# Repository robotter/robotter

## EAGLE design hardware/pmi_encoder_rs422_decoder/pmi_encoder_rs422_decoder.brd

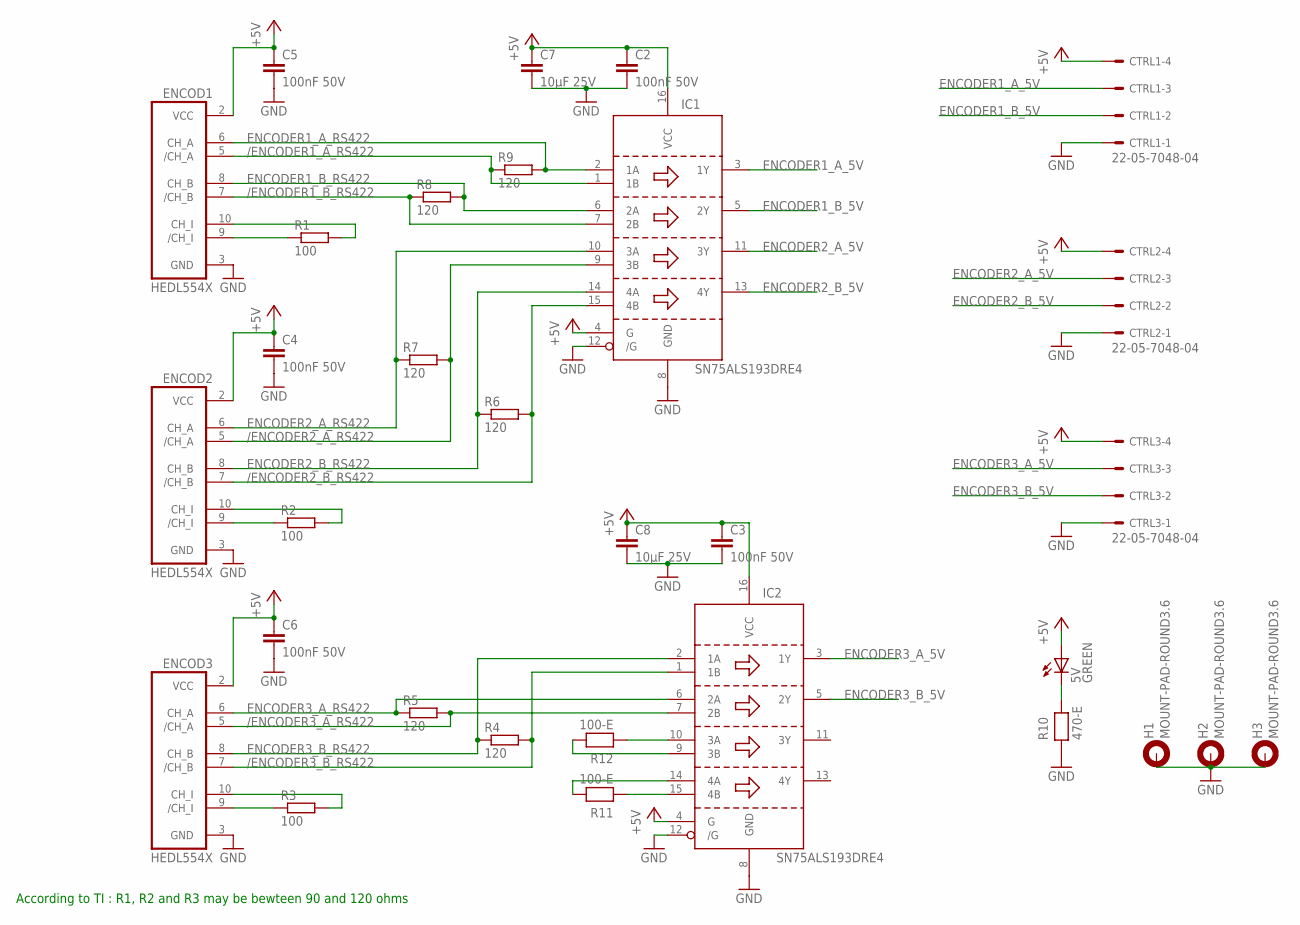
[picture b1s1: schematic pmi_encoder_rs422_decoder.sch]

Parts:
5V: GREEN; CHIP-LED0805
C2, C3, C4, C5, C6: 100nF 50V; C0805
C7, C8: 10µF 25V; C1210
CTRL1, CTRL2, CTRL3: 22-05-7048-04; 7395-04
ENCOD1, ENCOD2, ENCOD3: HEDL554X; ML10
H1, H2, H3: MOUNT-PAD-ROUND3.6; 3,6-PAD
IC1, IC2: SN75ALS193DRE4; SO16
R1, R2, R3: 100; 0207/7
R4, R5, R6, R7, R8, R9: 120; 0207/7
R10: 470-E; R0805
R11, R12: 100-E; R0805

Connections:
+5V: 5V.A, C2.1, C3.1, C4.1, C5.1, C6.1, C7.1, C8.1, CTRL1.4, CTRL2.4, CTRL3.4, ENCOD1.2 (VCC), ENCOD2.2 (VCC), ENCOD3.2 (VCC), IC1.4 (G), IC1.16 (VCC), IC2.4 (G), IC2.16 (VCC)
/ENCODER1_A_RS422: ENCOD1.5 (/CH_A), IC1.1 (1B), R9.1
/ENCODER1_B_RS422: ENCOD1.7 (/CH_B), IC1.7 (2B), R8.1
/ENCODER2_A_RS422: ENCOD2.5 (/CH_A), IC1.9 (3B), R7.2
/ENCODER2_B_RS422: ENCOD2.7 (/CH_B), IC1.15 (4B), R6.2
/ENCODER3_A_RS422: ENCOD3.5 (/CH_A), IC2.7 (2B), R5.2
/ENCODER3_B_RS422: ENCOD3.7 (/CH_B), IC2.1 (1B), R4.2
ENCODER1_A_5V: CTRL1.3, IC1.3 (1Y)
ENCODER1_A_RS422: ENCOD1.6 (CH_A), IC1.2 (1A), R9.2
ENCODER1_B_5V: CTRL1.2, IC1.5 (2Y)
ENCODER1_B_RS422: ENCOD1.8 (CH_B), IC1.6 (2A), R8.2
ENCODER2_A_5V: CTRL2.3, IC1.11 (3Y)
ENCODER2_A_RS422: ENCOD2.6 (CH_A), IC1.10 (3A), R7.1
ENCODER2_B_5V: CTRL2.2, IC1.13 (4Y)
ENCODER2_B_RS422: ENCOD2.8 (CH_B), IC1.14 (4A), R6.1
ENCODER3_A_5V: CTRL3.3, IC2.3 (1Y)
ENCODER3_A_RS422: ENCOD3.6 (CH_A), IC2.6 (2A), R5.1
ENCODER3_B_5V: CTRL3.2, IC2.5 (2Y)
ENCODER3_B_RS422: ENCOD3.8 (CH_B), IC2.2 (1A), R4.1
GND: C2.2, C3.2, C4.2, C5.2, C6.2, C7.2, C8.2, CTRL1.1, CTRL2.1, CTRL3.1, ENCOD1.3 (GND), ENCOD2.3 (GND), ENCOD3.3 (GND), H1.B3,6, H2.B3,6, H3.B3,6, IC1.8 (GND), IC1.12 (/G), IC2.8 (GND), IC2.12 (/G), R10.1
unnamed: ENCOD3.10 (CH_I), R3.2
unnamed: ENCOD3.9 (/CH_I), R3.1
unnamed: ENCOD2.9 (/CH_I), R2.1
unnamed: ENCOD2.10 (CH_I), R2.2
unnamed: ENCOD1.10 (CH_I), R1.2
unnamed: 5V.C, R10.2
unnamed: IC2.14 (4A), R11.2
unnamed: IC2.9 (3B), R12.2
unnamed: IC2.10 (3A), R12.1
unnamed: ENCOD1.9 (/CH_I), R1.1
unnamed: IC2.15 (4B), R11.1

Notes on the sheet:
According to TI : R1, R2 and R3 may be bewteen 90 and 120 ohms

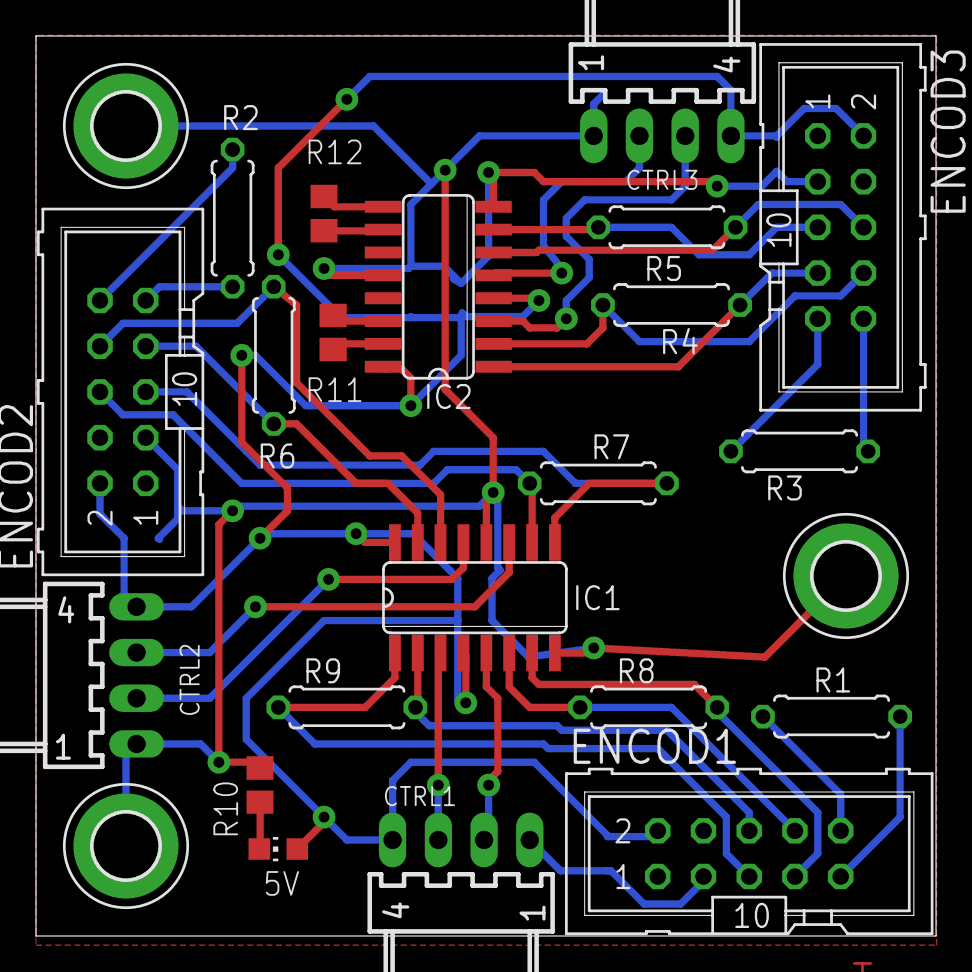
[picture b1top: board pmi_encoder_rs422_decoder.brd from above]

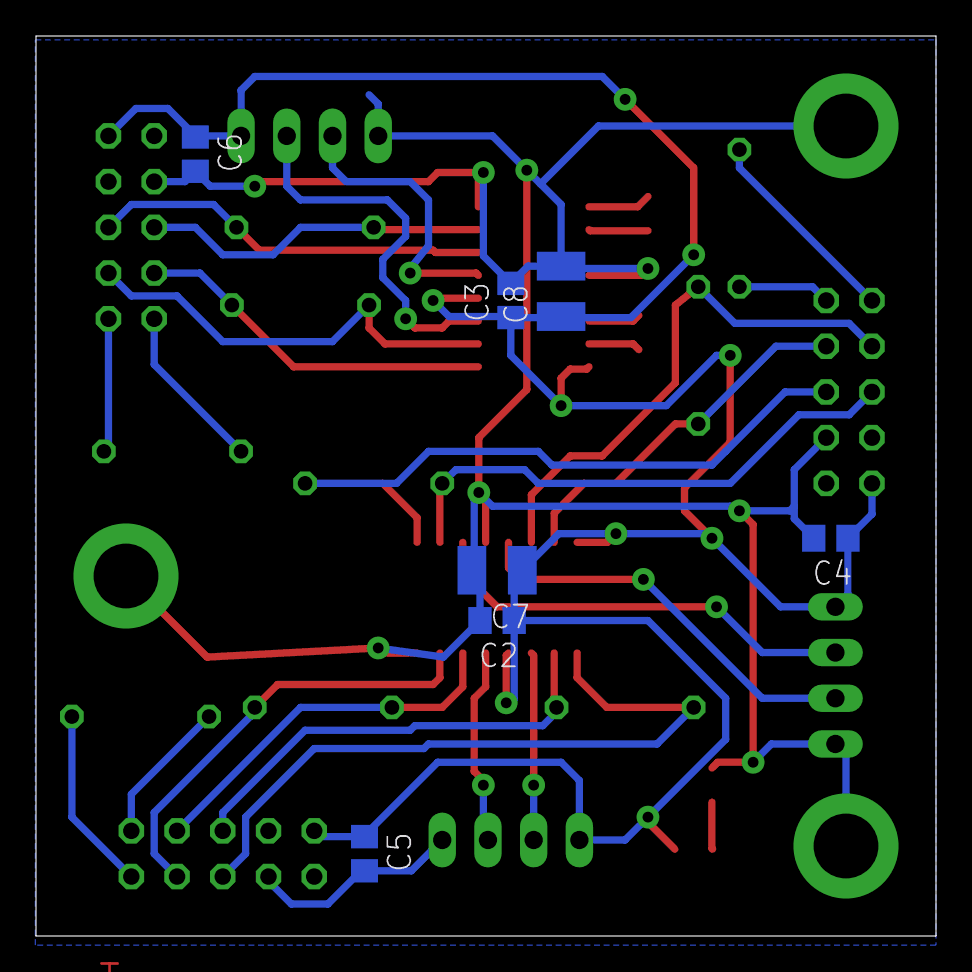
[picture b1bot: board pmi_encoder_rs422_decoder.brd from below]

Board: 2 copper layers, 50.0 x 50.0 mm, 31 parts (7 on the bottom side), 31 nets.

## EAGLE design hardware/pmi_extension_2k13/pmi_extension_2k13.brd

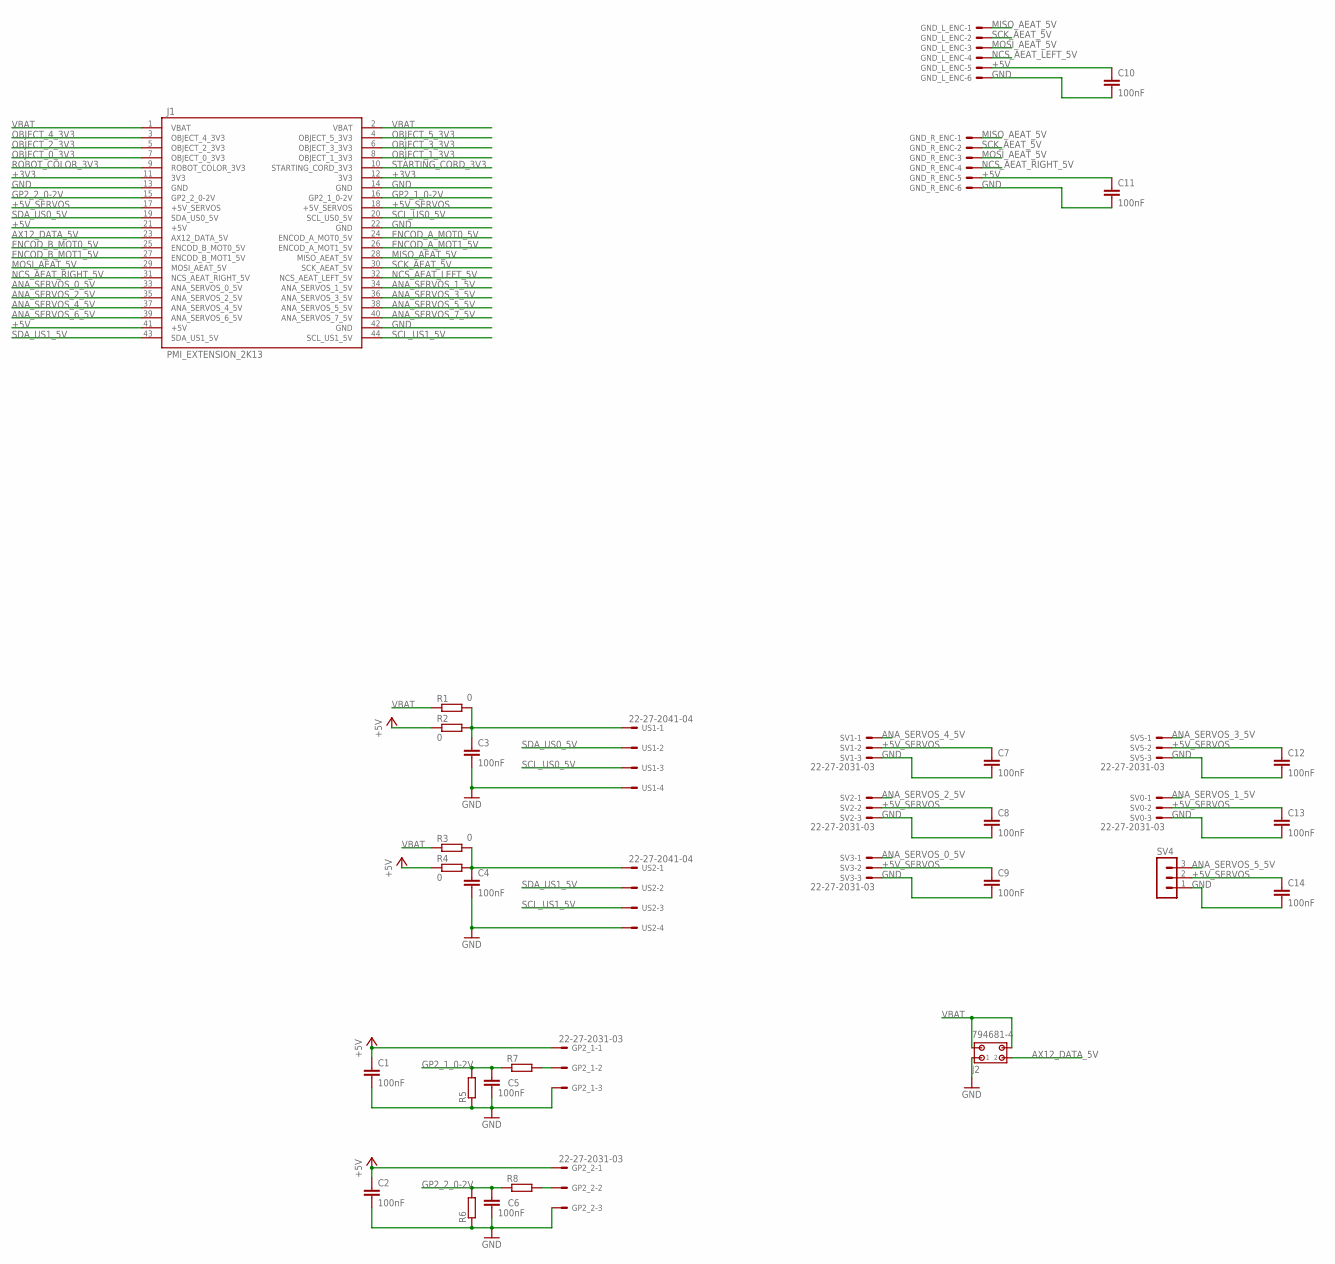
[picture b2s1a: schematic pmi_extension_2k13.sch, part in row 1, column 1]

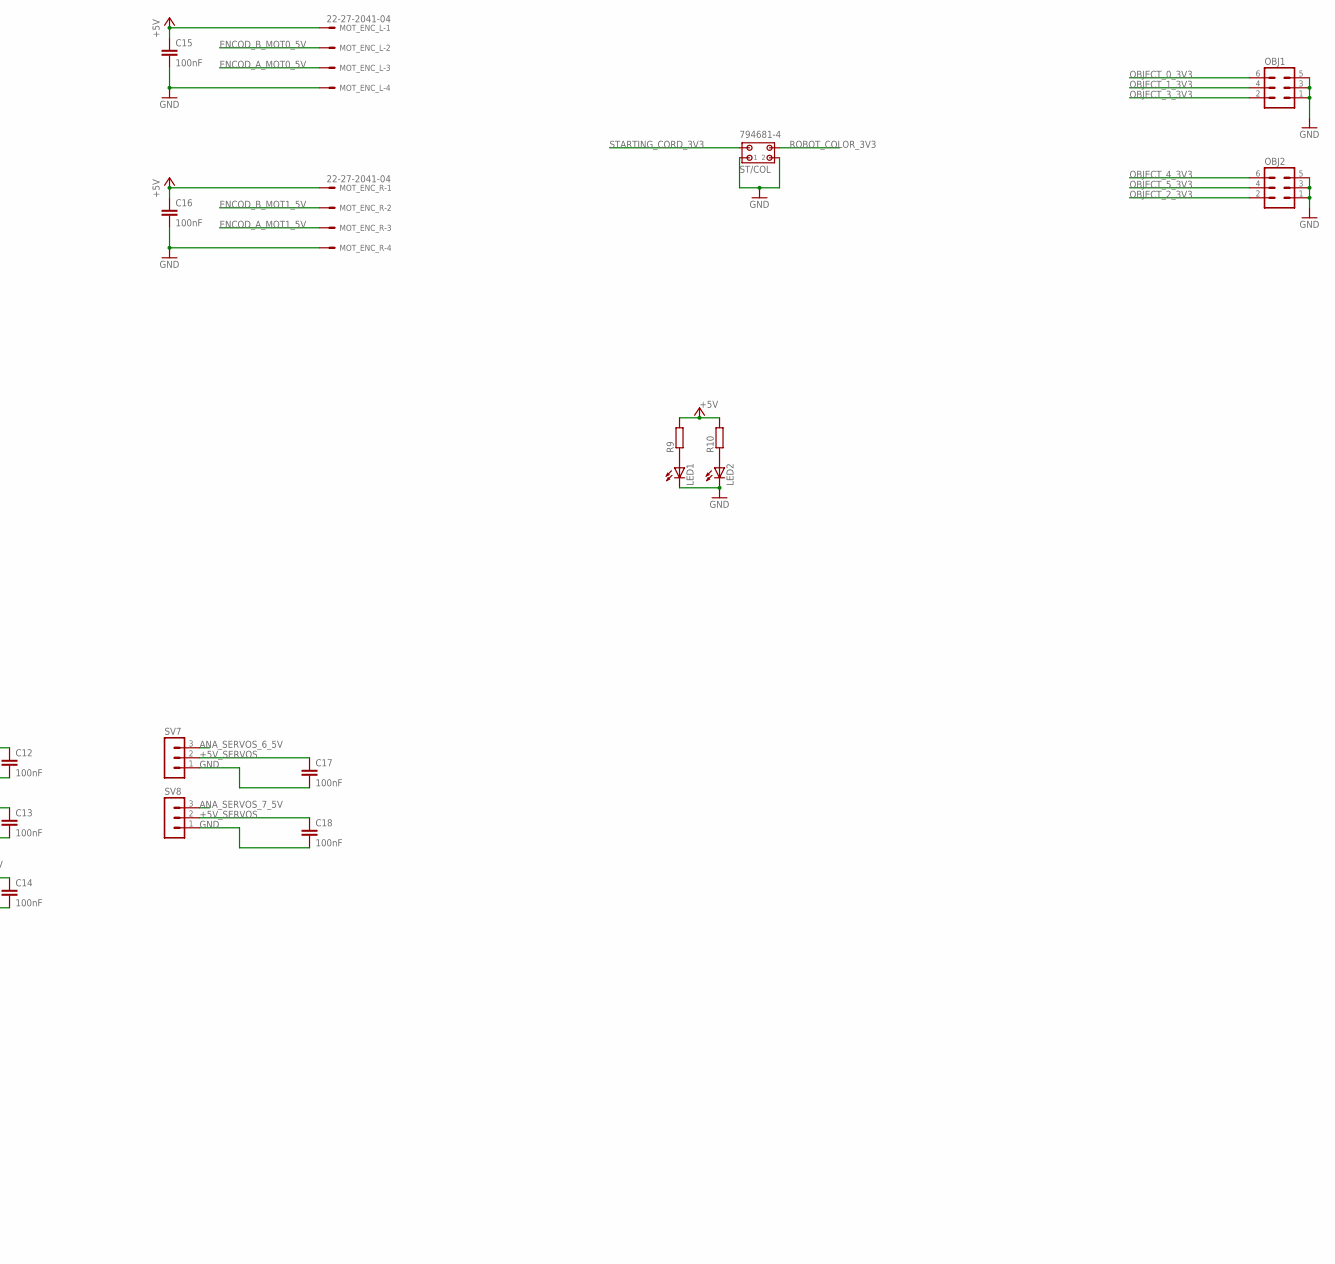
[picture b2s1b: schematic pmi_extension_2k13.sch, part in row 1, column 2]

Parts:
C1, C2, C3, C4, C5, C6, C10, C11, C14, C15, C16, C17, C18: 100nF; C0603
C7, C8, C9, C12, C13: 100nF; C0805
GND_L_ENC: 22-23-2061
GND_R_ENC: 22-23-2061
GP2_1, GP2_2: 22-27-2031-03; 6410-03
J1: PMI_EXTENSION_2K13; HEADER_2X22
J2: 794681-4
LED1, LED2: LED3MM
MOT_ENC_L: 22-27-2041-04; 6410-04
MOT_ENC_R: 22-27-2041-04; 6410-04
OBJ1, OBJ2: MA03-2
R1, R2, R3, R4: 0; R0603
R5, R6, R7, R8, R9, R10: R-EU_R0603; R0603
ST/COL: 794681-4
SV0, SV1, SV2, SV3, SV5: 22-27-2031-03; 6410-03
SV4, SV7, SV8: MA03-1
US1, US2: 22-27-2041-04; 6410-04

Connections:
+3V3: J1.11 (3V3), J1.12 (3V3)
+5V: C1.1, C2.1, C10.1, C11.1, C15.1, C16.1, GND_L_ENC.5, GND_R_ENC.5, GP2_1.1, GP2_2.1, J1.21 (+5V), J1.41 (+5V), MOT_ENC_L.1, MOT_ENC_R.1, R2.1, R4.1, R9.2, R10.2
+5V_SERVOS: C7.1, C8.1, C9.1, C12.1, C13.1, C14.1, C17.1, C18.1, J1.17 (+5V_SERVOS), J1.18 (+5V_SERVOS), SV0.2, SV1.2, SV2.2, SV3.2, SV4.2, SV5.2, SV7.2, SV8.2
ANA_SERVOS_0_5V: J1.33 (ANA_SERVOS_0_5V), SV3.1
ANA_SERVOS_1_5V: J1.34 (ANA_SERVOS_1_5V), SV0.1
ANA_SERVOS_2_5V: J1.35 (ANA_SERVOS_2_5V), SV2.1
ANA_SERVOS_3_5V: J1.36 (ANA_SERVOS_3_5V), SV5.1
ANA_SERVOS_4_5V: J1.37 (ANA_SERVOS_4_5V), SV1.1
ANA_SERVOS_5_5V: J1.38 (ANA_SERVOS_5_5V), SV4.3
ANA_SERVOS_6_5V: J1.39 (ANA_SERVOS_6_5V), SV7.3
ANA_SERVOS_7_5V: J1.40 (ANA_SERVOS_7_5V), SV8.3
AX12_DATA_5V: J1.23 (AX12_DATA_5V), J2.2
ENCOD_A_MOT0_5V: J1.24 (ENCOD_A_MOT0_5V), MOT_ENC_L.3
ENCOD_A_MOT1_5V: J1.26 (ENCOD_A_MOT1_5V), MOT_ENC_R.3
ENCOD_B_MOT0_5V: J1.25 (ENCOD_B_MOT0_5V), MOT_ENC_L.2
ENCOD_B_MOT1_5V: J1.27 (ENCOD_B_MOT1_5V), MOT_ENC_R.2
GND: C1.2, C2.2, C3.2, C4.2, C5.2, C6.2, C7.2, C8.2, C9.2, C10.2, C11.2, C12.2, C13.2, C14.2, C15.2, C16.2, C17.2, C18.2, GND_L_ENC.6, GND_R_ENC.6, GP2_1.3, GP2_2.3, J1.13 (GND), J1.14 (GND), J1.22 (GND), J1.42 (GND), J2.1, LED1.K (C), LED2.K (C), MOT_ENC_L.4, MOT_ENC_R.4, OBJ1.1, OBJ1.3, OBJ1.5, OBJ2.1, OBJ2.3, OBJ2.5, R5.1, R6.1, ST/COL.1, ST/COL.2, SV0.3, SV1.3, SV2.3, SV3.3, SV4.1, SV5.3, SV7.1, SV8.1, US1.4, US2.4
GP2_1_0-2V: C5.1, J1.16 (GP2_1_0-2V), R5.2, R7.1
GP2_2_0-2V: C6.1, J1.15 (GP2_2_0-2V), R6.2, R8.1
MISO_AEAT_5V: GND_L_ENC.1, GND_R_ENC.1, J1.28 (MISO_AEAT_5V)
MOSI_AEAT_5V: GND_L_ENC.3, GND_R_ENC.3, J1.29 (MOSI_AEAT_5V)
unnamed: GP2_1.2, R7.2
unnamed: GP2_2.2, R8.2
unnamed: C4.1, R3.2, R4.2, US2.1
unnamed: LED1.A, R9.1
unnamed: C3.1, R1.2, R2.2, US1.1
unnamed: LED2.A, R10.1
NCS_AEAT_LEFT_5V: GND_L_ENC.4, J1.32 (NCS_AEAT_LEFT_5V)
NCS_AEAT_RIGHT_5V: GND_R_ENC.4, J1.31 (NCS_AEAT_RIGHT_5V)
OBJECT_0_3V3: J1.7 (OBJECT_0_3V3), OBJ1.6
OBJECT_1_3V3: J1.8 (OBJECT_1_3V3), OBJ1.4
OBJECT_2_3V3: J1.5 (OBJECT_2_3V3), OBJ2.2
OBJECT_3_3V3: J1.6 (OBJECT_3_3V3), OBJ1.2
OBJECT_4_3V3: J1.3 (OBJECT_4_3V3), OBJ2.6
OBJECT_5_3V3: J1.4 (OBJECT_5_3V3), OBJ2.4
ROBOT_COLOR_3V3: J1.9 (ROBOT_COLOR_3V3), ST/COL.4
SCK_AEAT_5V: GND_L_ENC.2, GND_R_ENC.2, J1.30 (SCK_AEAT_5V)
SCL_US0_5V: J1.20 (SCL_US0_5V), US1.3
SCL_US1_5V: J1.44 (SCL_US1_5V), US2.3
SDA_US0_5V: J1.19 (SDA_US0_5V), US1.2
SDA_US1_5V: J1.43 (SDA_US1_5V), US2.2
STARTING_CORD_3V3: J1.10 (STARTING_CORD_3V3), ST/COL.3
VBAT: J1.1 (VBAT), J1.2 (VBAT), J2.3, J2.4, R1.1, R3.1

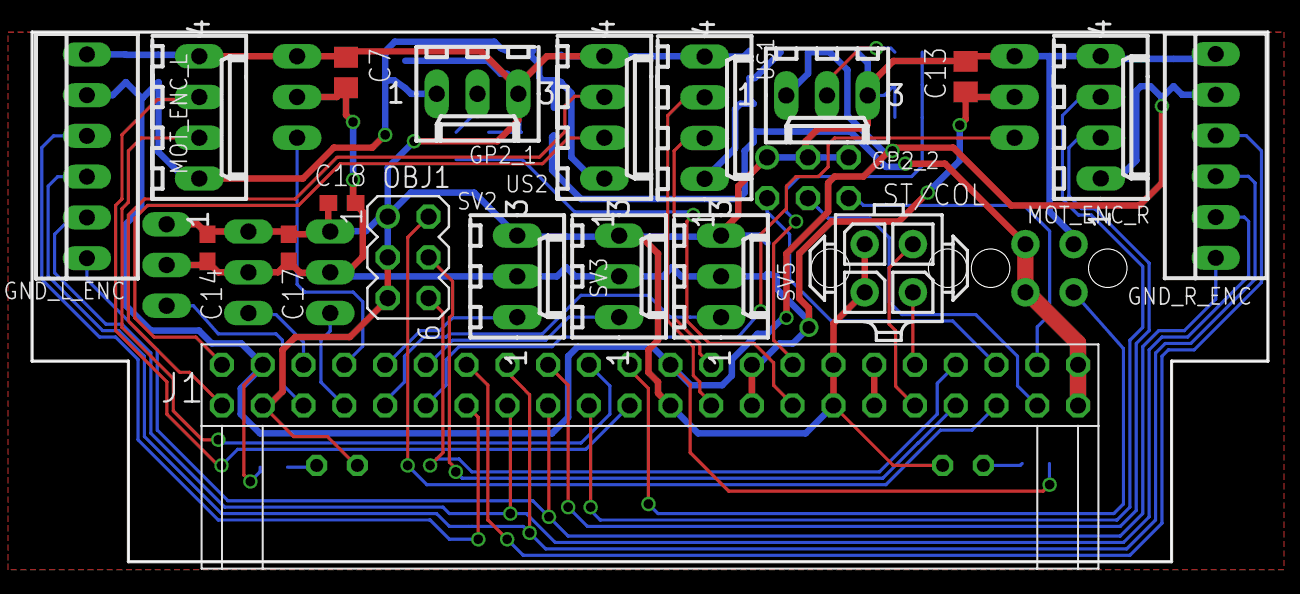
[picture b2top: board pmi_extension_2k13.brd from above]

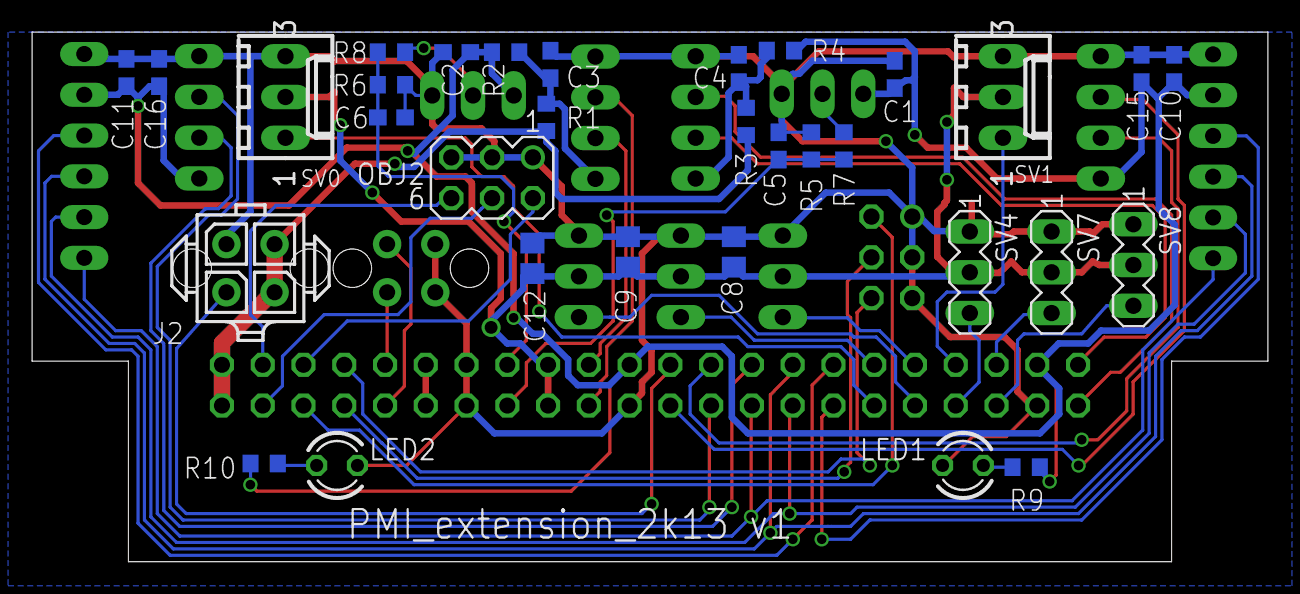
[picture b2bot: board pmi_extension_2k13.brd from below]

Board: 2 copper layers, 77.0 x 33.0 mm, 51 parts (32 on the bottom side), 43 nets.

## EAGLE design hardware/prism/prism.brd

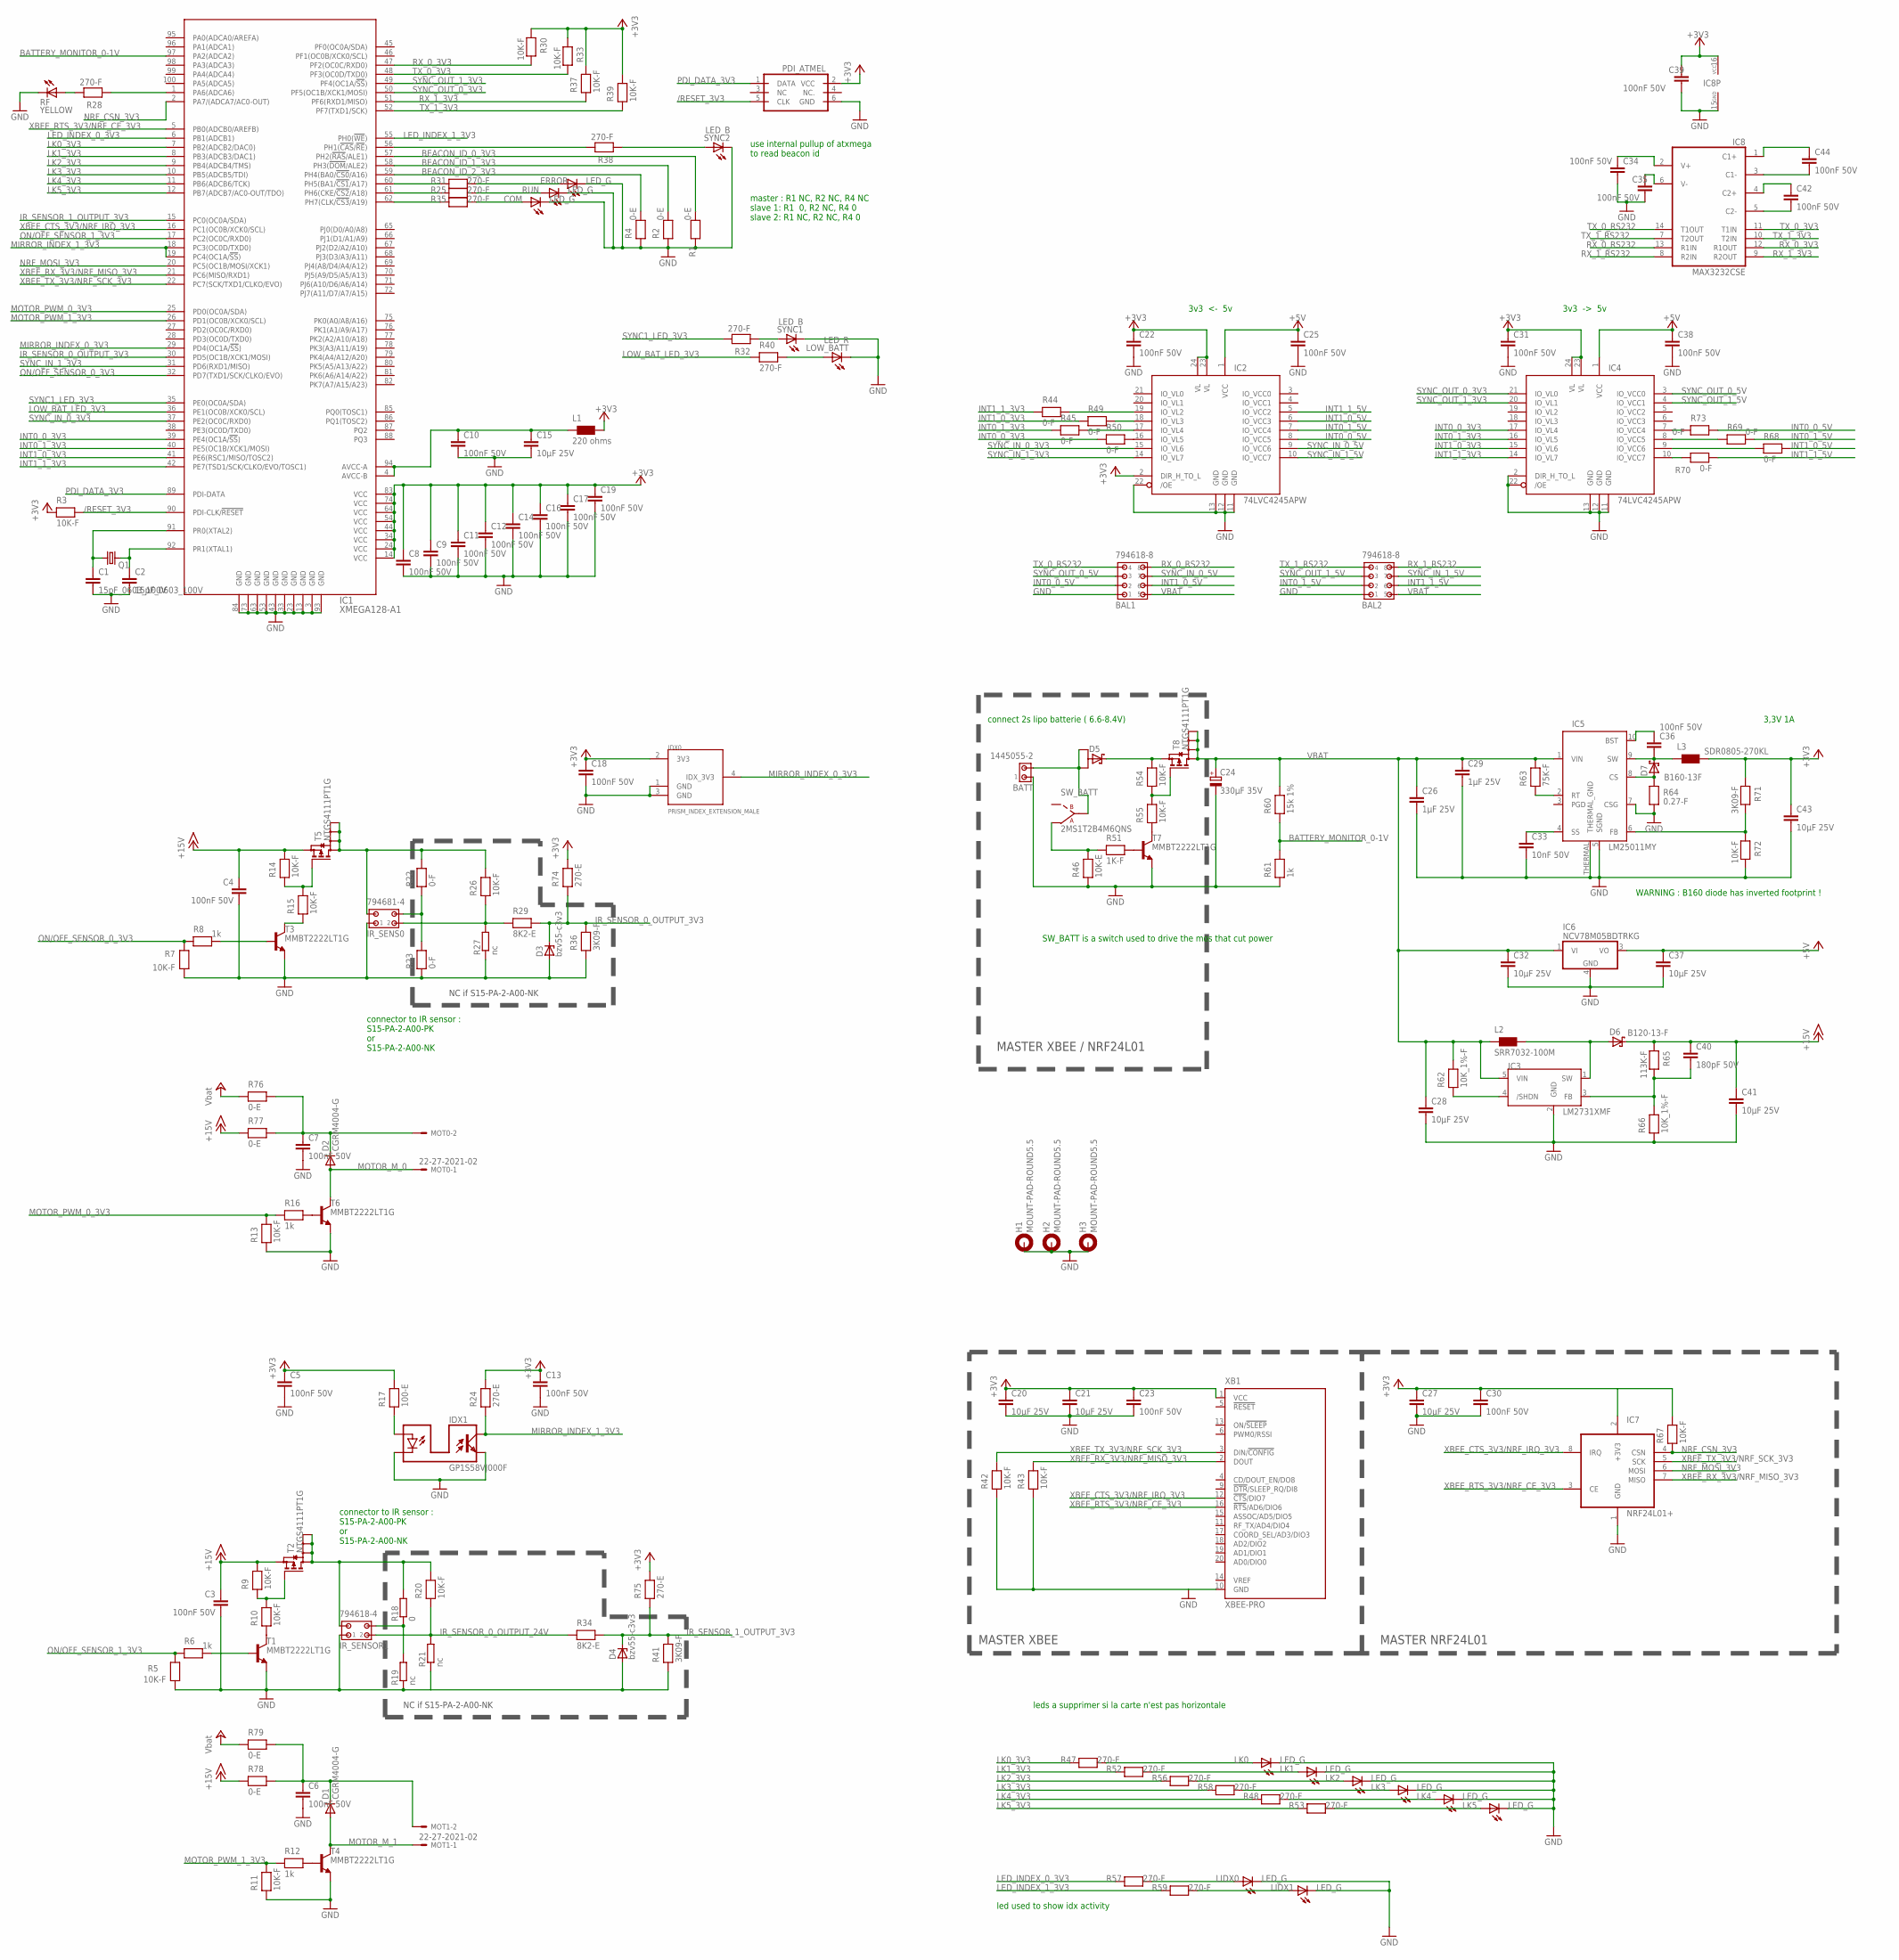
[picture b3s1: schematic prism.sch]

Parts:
BAL1, BAL2: 794618-8
BATT: 1445055-2
C1, C2: 15pF_0603_100V; C0603
C3, C4, C5, C6, C7, C8, C9, C10, C11, C12, C13, C14, C16, C17, C18, C19, C22, C23, C25, C30, C31, C34, C35, C36, C38, C39, C42, C44: 100nF 50V; C0603
C15, C20, C21, C27, C28, C32, C37, C41, C43: 10µF 25V; C1210
C24: 330µF 35V; PANASONIC_G
C26, C29: 1µF 25V; C1206
C33: 10nF 50V; C0603
C40: 180pF 50V; C0603
COM: LED_G; CHIP-LED0805
D1, D2: CGRM4004-G; SOD-123_MINI-SMA
D3, D4: bzv55-c3v3; SOD80C
D5: 50WQ03; TO252
D6: B120-13-F; SMB
D7: B160-13F; SMA
ERROR: LED_G; CHIP-LED0805
H1, H2, H3: MOUNT-PAD-ROUND5.5; 5,5-PAD
IC1: XMEGA128-A1; TQFP100
IC2, IC4: 74LVC4245APW; TSSOP24
IC3: LM2731XMF; SOT23-5
IC5: LM25011MY; MSOP10_THERMAL
IC6: NCV78M05BDTRKG; DPACK_3
IC7: NRF24L01+
IC8: MAX3232CSE; SO16
IDX0: PRISM_INDEX_EXTENSION_MALE
IDX1: GP1S58VJ000F
IR_SENS0: 794681-4
IR_SENSOR1: 794618-4
L1: 220 ohms; R0603
L2: SRR7032-100M; SRR7032
L3: SDR0805-270KL; SDR0805
LIDX0, LIDX1: LED_G; CHIP-LED0805
LK0, LK1, LK2, LK3, LK4, LK5: LED_G; CHIP-LED0805
LOW_BATT: LED_R; CHIP-LED0805
MOT0, MOT1: 22-27-2021-02; 6410-02
PDI_ATMEL: PDI_ATMELL; ML6L
Q1: CRYSTAL_16MHZ_HC49UP; HC49UP
R1, R2, R4, R76, R77, R78, R79: 0-E; R0805
R3, R5, R7, R9, R10, R11, R13, R14, R15, R20, R26, R30, R33, R37, R39, R42, R43, R54, R55, R67, R72: 10K-F; R0603
R6, R8, R12, R16: 1k; R0603
R17: 100-E; R0805
R18: 0; R0603
R19, R21, R27: nc; R0603
R22, R23, R44, R45, R49, R50, R68, R69, R70, R73: 0-F; R0603
R24, R74, R75: 270-E; R0805
R25, R28, R31, R32, R35, R38, R40, R47, R48, R52, R53, R56, R57, R58, R59: 270-F; R0603
R29, R34: 8K2-E; R0805
R36, R41, R71: 3K09-F; R0603
R46: 10K-E; R0805
R51: 1K-F; R0603
R60: 15k 1%; R0805
R61: 1k; R0805
R62, R66: 10K_1%-F; R0603
R63: 75K-F; R0603
R64: 0.27-F; R0603
R65: 113K-F; R0603
RF: YELLOW; CHIP-LED0805
RUN: LED_G; CHIP-LED0805
SW_BATT: 2MS1T2B4M6QNS
SYNC1, SYNC2: LED_B; CHIP-LED0805
T1, T3, T4, T6, T7: MMBT2222LT1G; SOT23-BEC
T2, T5, T8: NTGS4111PT1G; TSOP-6
XB1: XBEE-PRO

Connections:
+3V3: C5.1, C8.1, C9.1, C11.1, C12.1, C13.1, C14.1, C16.1, C17.1, C18.1, C19.1, C20.1, C21.1, C22.1, C23.1, C27.1, C30.1, C31.1, C39.1, C43.1, IC1.14 (VCC), IC1.24 (VCC), IC1.34 (VCC), IC1.44 (VCC), IC1.54 (VCC), IC1.64 (VCC), IC1.74 (VCC), IC1.83 (VCC), IC2.2 (DIR_H_TO_L), IC2.23 (VL), IC2.24 (VL), IC4.23 (VL), IC4.24 (VL), IC7.2 (+3V3), IC8.16 (VCC), IDX0.2 (3V3), L1.2, L3.2, PDI_ATMEL.2 (VCC), R3.1, R17.2, R24.2, R30.1, R33.1, R37.2, R39.2, R67.2, R71.1, R74.2, R75.2, XB1.1 (VCC)
+5V: C25.1, C37.1, C38.1, IC2.1 (VCC), IC4.1 (VCC), IC6.3 (VO)
+15V: C3.1, C4.1, C40.1, C41.1, D6.C, R9.2, R14.2, R65.1, R77.1, R78.1, T2.4 (S), T5.4 (S)
/RESET_3V3: IC1.90 (PDI-CLK/!RESET), PDI_ATMEL.5 (CLK), R3.2
BATTERY_MONITOR_0-1V: IC1.97 (PA2(ADCA2)), R60.1, R61.2
BEACON_ID_0_3V3: IC1.57 (PH2(!RAS!/ALE1)), R1.2
BEACON_ID_1_3V3: IC1.58 (PH3(!DOM!/ALE2)), R2.2
BEACON_ID_2_3V3: IC1.59 (PH4(BA0/!CS0!/A16)), R4.2
GND: BAL1.1, BAL2.1, BATT.1, C1.2, C2.2, C3.2, C4.2, C5.2, C6.2, C7.2, C8.2, C9.2, C10.2, C11.2, C12.2, C13.2, C14.2, C15.2, C16.2, C17.2, C18.2, C19.2, C20.2, C21.2, C22.2, C23.2, C24.-, C25.2, C26.2, C27.2, C28.2, C29.2, C30.2, C31.2, C32.2, C33.2, C34.2, C35.2, C37.2, C38.2, C39.2, C41.2, C43.2, COM.C, D3.A, D4.A, ERROR.C, H1.B5,5, H2.B5,5, H3.B5,5, IC1.3 (GND), IC1.13 (GND), IC1.23 (GND), IC1.33 (GND), IC1.43 (GND), IC1.53 (GND), IC1.63 (GND), IC1.73 (GND), IC1.84 (GND), IC1.93 (GND), IC2.11 (GND), IC2.12 (GND), IC2.13 (GND), IC2.22 (/OE), IC3.2 (GND), IC4.2 (DIR_H_TO_L), IC4.11 (GND), IC4.12 (GND), IC4.13 (GND), IC4.22 (/OE), IC5.5 (SGND), IC5.7 (CSG), IC5.THERMAL (THERMAL_GND), IC6.4 (GND), IC7.1 (GND), IC8.15 (GND), IDX0.1 (GND), IDX0.3 (GND), IDX1.LED_C, IDX1.TRANSISTOR_E, IR_SENS0.1, IR_SENSOR1.1, LIDX0.C, LIDX1.C, LK0.C, LK1.C, LK2.C, LK3.C, LK4.C, LK5.C, LOW_BATT.C, PDI_ATMEL.6 (GND), R1.1, R2.1, R4.1, R5.1, R7.1, R11.1, R13.1, R19.1, R21.1, R23.1, R27.1, R36.1, R41.1, R42.1, R43.1, R46.1, R61.1, R64.1, R66.1, R72.2, RF.C, RUN.C, SYNC1.C, SYNC2.C, T1.E, T3.E, T4.E, T6.E, T7.E, XB1.10 (GND)
INT0_0_3V3: IC1.39 (PE4(OC1A/!SS!)), IC4.17 (IO_VL4), R50.1
INT0_0_5V: BAL1.2, IC2.8 (IO_VCC5), R73.2
INT0_1_3V3: IC1.40 (PE5(OC1B/XCK1/MOSI)), IC4.16 (IO_VL5), R45.1
INT0_1_5V: BAL2.2, IC2.7 (IO_VCC4), R69.2
INT1_0_3V3: IC1.41 (PE6(RSC1/MISO/TOSC2)), IC4.15 (IO_VL6), R49.1
INT1_0_5V: BAL1.6, IC2.6 (IO_VCC3), R68.2
INT1_1_3V3: IC1.42 (PE7(TSD1/SCK/CLKO/EVO/TOSC1)), IC4.14 (IO_VL7), R44.1
INT1_1_5V: BAL2.6, IC2.5 (IO_VCC2), R70.2
IR_SENSOR_0_OUTPUT_3V3: D3.C, IC1.30 (PD5(OC1B/XCK1/MOSI)), R29.2, R36.2, R74.1
IR_SENSOR_0_OUTPUT_24V: IR_SENSOR1.2, R20.1, R21.2, R34.1
IR_SENSOR_1_OUTPUT_3V3: D4.C, IC1.15 (PC0(OC0A/SDA)), R34.2, R41.2, R75.1
IR_SENSOR_1_OUTPUT_24V: IR_SENS0.2, R26.1, R27.2, R29.1
LED_INDEX_0_3V3: IC1.6 (PB1(ADCB1)), R57.1
LED_INDEX_1_3V3: IC1.55 (PH0(!WE!)), R59.1
LK0_3V3: IC1.7 (PB2(ADCB2/DAC0)), R47.1
LK1: LK2.A, R56.2
LK1_3V3: IC1.8 (PB3(ADCB3/DAC1)), R52.1
LK2_3V3: IC1.9 (PB4(ADCB4/TMS)), R56.1
LK3_3V3: IC1.10 (PB5(ADCB5/TDI)), R58.1
LK4_3V3: IC1.11 (PB6(ADCB6/TCK)), R48.1
LK5: LIDX0.A, R57.2
LK5_3V3: IC1.12 (PB7(ADCB7/AC0-OUT/TDO)), R53.1
LOW_BAT_LED_3V3: IC1.36 (PE1(OC0B/XCK0/SCL)), R40.1
MIRROR_INDEX_0_3V3: IC1.29 (PD4(OC1A/!SS!)), IDX0.4 (IDX_3V3)
MIRROR_INDEX_1_3V3: IC1.18 (PC3(OC0D/TXD0)), IC1.19 (PC4(OC1A/!SS!)), IDX1.TRANSISTOR_C, R24.1
MOTOR_M_0: D2.A, MOT0.1, T6.C
MOTOR_M_1: D1.A, MOT1.1, T4.C
MOTOR_PWM_0_3V3: IC1.25 (PD0(OC0A/SDA)), R13.2, R16.1
MOTOR_PWM_1_3V3: IC1.26 (PD1(OC0B/XCK0/SCL)), R11.2, R12.1
unnamed: C44.1, IC8.1 (C1+)
unnamed: R25.2, RUN.A
unnamed: R12.2, T4.B
unnamed: ERROR.A, R31.2
unnamed: C44.2, IC8.3 (C1-)
unnamed: C42.1, IC8.4 (C2+)
unnamed: COM.A, R35.2
unnamed: C10.1, C15.1, IC1.4 (AVCC-B), IC1.94 (AVCC-A), L1.1
unnamed: IC1.61 (PH6(CKE/!CS2!/A18)), R25.1
unnamed: IC1.60 (PH5(BA1/!CS1!/A17)), R31.1
unnamed: C34.1, IC8.2 (V+)
unnamed: IC1.62 (PH7(CLK/!CS3!/A19)), R35.1
unnamed: C35.1, IC8.6 (V-)
unnamed: R14.1, R15.2, T5.3 (G)
unnamed: R8.2, T3.B
unnamed: R15.1, T3.C
unnamed: R16.2, T6.B
unnamed: LK0.A, R47.2
unnamed: LK1.A, R52.2
unnamed: LK3.A, R58.2
unnamed: BATT.2, D5.1 (A1), D5.3 (A2), SW_BATT.2 (1)
unnamed: C42.2, IC8.5 (C2-)
unnamed: R51.2, T7.B
unnamed: R54.1, R55.2, T8.3 (G)
unnamed: R28.2, RF.A
unnamed: IC1.1 (PA6(ADCA6)), R28.1
unnamed: R55.1, T7.C
unnamed: D5.4 (C), R54.2, T8.4 (S)
unnamed: IC1.56 (PH1(!CAS!/!RE!)), R38.2
unnamed: R38.1, SYNC2.A
unnamed: LOW_BATT.A, R40.2
unnamed: R32.1, SYNC1.A
unnamed: R6.2, T1.B
unnamed: C36.2, D7.C, IC5.9 (SW), L3.1
unnamed: D7.A, IC5.8 (CS), R64.2
unnamed: IC5.2 (RT), R63.1
unnamed: IR_SENS0.4, R22.1, R23.2
unnamed: R10.1, T1.C
unnamed: C33.1, IC5.4 (SS)
unnamed: IC5.6 (FB), R71.2, R72.1
unnamed: C1.1, IC1.91 (PR0(XTAL2)), Q1.1
unnamed: C2.1, IC1.92 (PR1(XTAL1)), Q1.2
unnamed: IC4.10 (IO_VCC7), R70.1
unnamed: C36.1, IC5.10 (BST)
unnamed: IC2.19 (IO_VL2), R44.2
unnamed: IC2.17 (IO_VL4), R45.2
unnamed: IC2.18 (IO_VL3), R49.2
unnamed: IC2.16 (IO_VL5), R50.2
unnamed: IC4.9 (IO_VCC6), R68.1
unnamed: IC4.7 (IO_VCC4), R73.1
unnamed: IC4.8 (IO_VCC5), R69.1
unnamed: IR_SENSOR1.3, R18.2, R20.2, T2.1 (D), T2.2 (D), T2.5 (D), T2.6 (D)
unnamed: IDX1.LED_A, R17.1
unnamed: IR_SENS0.3, R22.2, R26.2, T5.1 (D), T5.2 (D), T5.5 (D), T5.6 (D)
unnamed: D6.A, IC3.1 (SW), L2.2
unnamed: C40.2, IC3.3 (FB), R65.2, R66.2
unnamed: IC3.4 (/SHDN), R62.1
unnamed: LK4.A, R48.2
unnamed: LK5.A, R53.2
unnamed: LIDX1.A, R59.2
unnamed: R9.1, R10.2, T2.3 (G)
unnamed: IR_SENSOR1.4, R18.1, R19.2
NRF_CSN_3V3: IC1.2 (PA7/(ADCA7/AC0-OUT)), IC7.4 (CSN), R67.1
NRF_MOSI_3V3: IC1.20 (PC5(OC1B/MOSI/XCK1)), IC7.6 (MOSI)
ON/OFF_SENSOR_0_3V3: IC1.32 (PD7(TXD1/SCK/CLKO/EVO)), R7.2, R8.1
ON/OFF_SENSOR_1_3V1: R46.2, R51.1, SW_BATT.3
ON/OFF_SENSOR_1_3V3: IC1.17 (PC2(OC0C/RXD0)), R5.2, R6.1
PDI_DATA_3V3: IC1.89 (PDI-DATA), PDI_ATMEL.1 (DATA)
RX_0_3V3: IC1.47 (PF2(OC0C/RXD0)), IC8.12 (R1OUT), R30.2
RX_0_RS232: BAL1.8, IC8.13 (R1IN)
RX_1_3V3: IC1.51 (PF6(RXD1/MISO)), IC8.9 (R2OUT), R37.1
RX_1_RS232: BAL2.8, IC8.8 (R2IN)
SYNC1_LED_3V3: IC1.35 (PE0(OC0A/SDA)), R32.2
SYNC_IN_0_3V3: IC1.37 (PE2(OC0C/RXD0)), IC2.15 (IO_VL6)
SYNC_IN_0_5V: BAL1.7, IC2.9 (IO_VCC6)
SYNC_IN_1_3V3: IC1.31 (PD6(RXD1/MISO)), IC2.14 (IO_VL7)
SYNC_IN_1_5V: BAL2.7, IC2.10 (IO_VCC7)
SYNC_OUT_0_3V3: IC1.50 (PF5(OC1B/XCK1/MOSI)), IC4.21 (IO_VL0)
SYNC_OUT_0_5V: BAL1.3, IC4.3 (IO_VCC0)
SYNC_OUT_1_3V3: IC1.49 (PF4(OC1A/!SS!)), IC4.20 (IO_VL1)
SYNC_OUT_1_5V: BAL2.3, IC4.4 (IO_VCC1)
TX_0_3V3: IC1.48 (PF3(OC0D/TXD0)), IC8.11 (T1IN), R33.2
TX_0_RS232: BAL1.4, IC8.14 (T1OUT)
TX_1_3V3: IC1.52 (PF7(TXD1/SCK)), IC8.10 (T2IN), R39.1
TX_1_RS232: BAL2.4, IC8.7 (T2OUT)
VBAT: BAL1.5, BAL2.5, C24.+, C26.1, C28.1, C29.1, C32.1, IC3.5 (VIN), IC5.1 (VIN), IC6.1 (VI), L2.1, R60.2, R62.2, R63.2, R76.1, R79.1, T8.1 (D), T8.2 (D), T8.5 (D), T8.6 (D)
VCC_MOT0: C7.1, D2.C, MOT0.2, R76.2, R77.2
VCC_MOT1: C6.1, D1.C, MOT1.2, R78.2, R79.2
XBEE_CTS_3V3/NRF_IRQ_3V3: IC1.16 (PC1(OC0B/XCK0/SCL)), IC7.8 (IRQ), XB1.12 (!CTS!/DIO7)
XBEE_RTS_3V3/NRF_CE_3V3: IC1.5 (PB0(ADCB0/AREFB)), IC7.3 (CE), XB1.16 (!RTS!/AD6/DIO6)
XBEE_RX_3V3/NRF_MISO_3V3: IC1.21 (PC6(MISO/RXD1)), IC7.7 (MISO), R43.2, XB1.2 (DOUT)
XBEE_TX_3V3/NRF_SCK_3V3: IC1.22 (PC7(SCK/TXD1/CLKO/EVO)), IC7.5 (SCK), R42.2, XB1.3 (DIN/!CONFIG)

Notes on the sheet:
leds a supprimer si la carte n'est pas horizontale
3v3 <- 5v
3v3 -> 5v
connect 2s lipo batterie ( 6.6-8.4V)
use internal pullup of atxmega to read beacon id
SW_BATT is a switch used to drive the mos that cut power
led used to show idx activity
3,3V 1A
connector to IR sensor : S15-PA-2-A00-PK or S15-PA-2-A00-NK
MASTER XBEE
MASTER NRF24L01
MASTER XBEE / NRF24L01
WARNING : B160 diode has inverted footprint !
master : R1 NC, R2 NC, R4 NC slave 1: R1 0, R2 NC, R4 0 slave 2: R1 NC, R2 NC, R4 0
NC if S15-PA-2-A00-NK
